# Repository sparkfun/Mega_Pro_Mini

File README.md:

**NOTE:** *This product has been retired from our catalog. If you are looking for more up-to-date info, please check out some of these resources to see how other users are still hacking and improving on this product.*
* *[SparkFun Forum](https://forum.sparkfun.com/)*
* *[Comments Here on GitHub](https://github.com/sparkfun/Mega_Pro_Mini/issues)*
* *[IRC Channel](https://www.sparkfun.com/news/263)*

SparkFun Mega Pro Mini - 3.3V
========================================

[*SparkFun Mega Pro Mini - 3.3V (DEV-10743)*](https://www.sparkfun.com/products/10743)

 This is a 3.3V microcontroller running a version of the stk500v2 bootloader at 8MHz. 
 In order to shrink the Mega Pro down to its minimum footprint, we’ve condensed the board layout, removed the barrel jack footprint and replaced the traditional Arduino-style headers with compact vertical JST connectors.

 Repository Contents
-------------------

* **/Hardware** - Eagle design files (.brd, .sch)
* **/Production** - Production panel files (.brd)

Documentation
--------------
* **[Board Definition Files](https://github.com/sparkfun/Arduino_Boards)** - Board Definition files for Mega Pro Mini. 
* **[SparkFun Fritzing repo](https://github.com/sparkfun/Fritzing_Parts)** - Fritzing diagrams for SparkFun products.
* **[SparkFun 3D Model repo](https://github.com/sparkfun/3D_Models)** - 3D models of SparkFun products. 

License Information
-------------------
This product is _**open source**_! 

The **hardware** is released under [Creative Commons ShareAlike 4.0 International](https://creativecommons.org/licenses/by-sa/4.0/).

Please use, reuse, and modify these files as you see fit. Please maintain attribution to SparkFun Electronics and release anything derivative under the same license.

Distributed as-is; no warranty is given.

- Your friends at SparkFun.

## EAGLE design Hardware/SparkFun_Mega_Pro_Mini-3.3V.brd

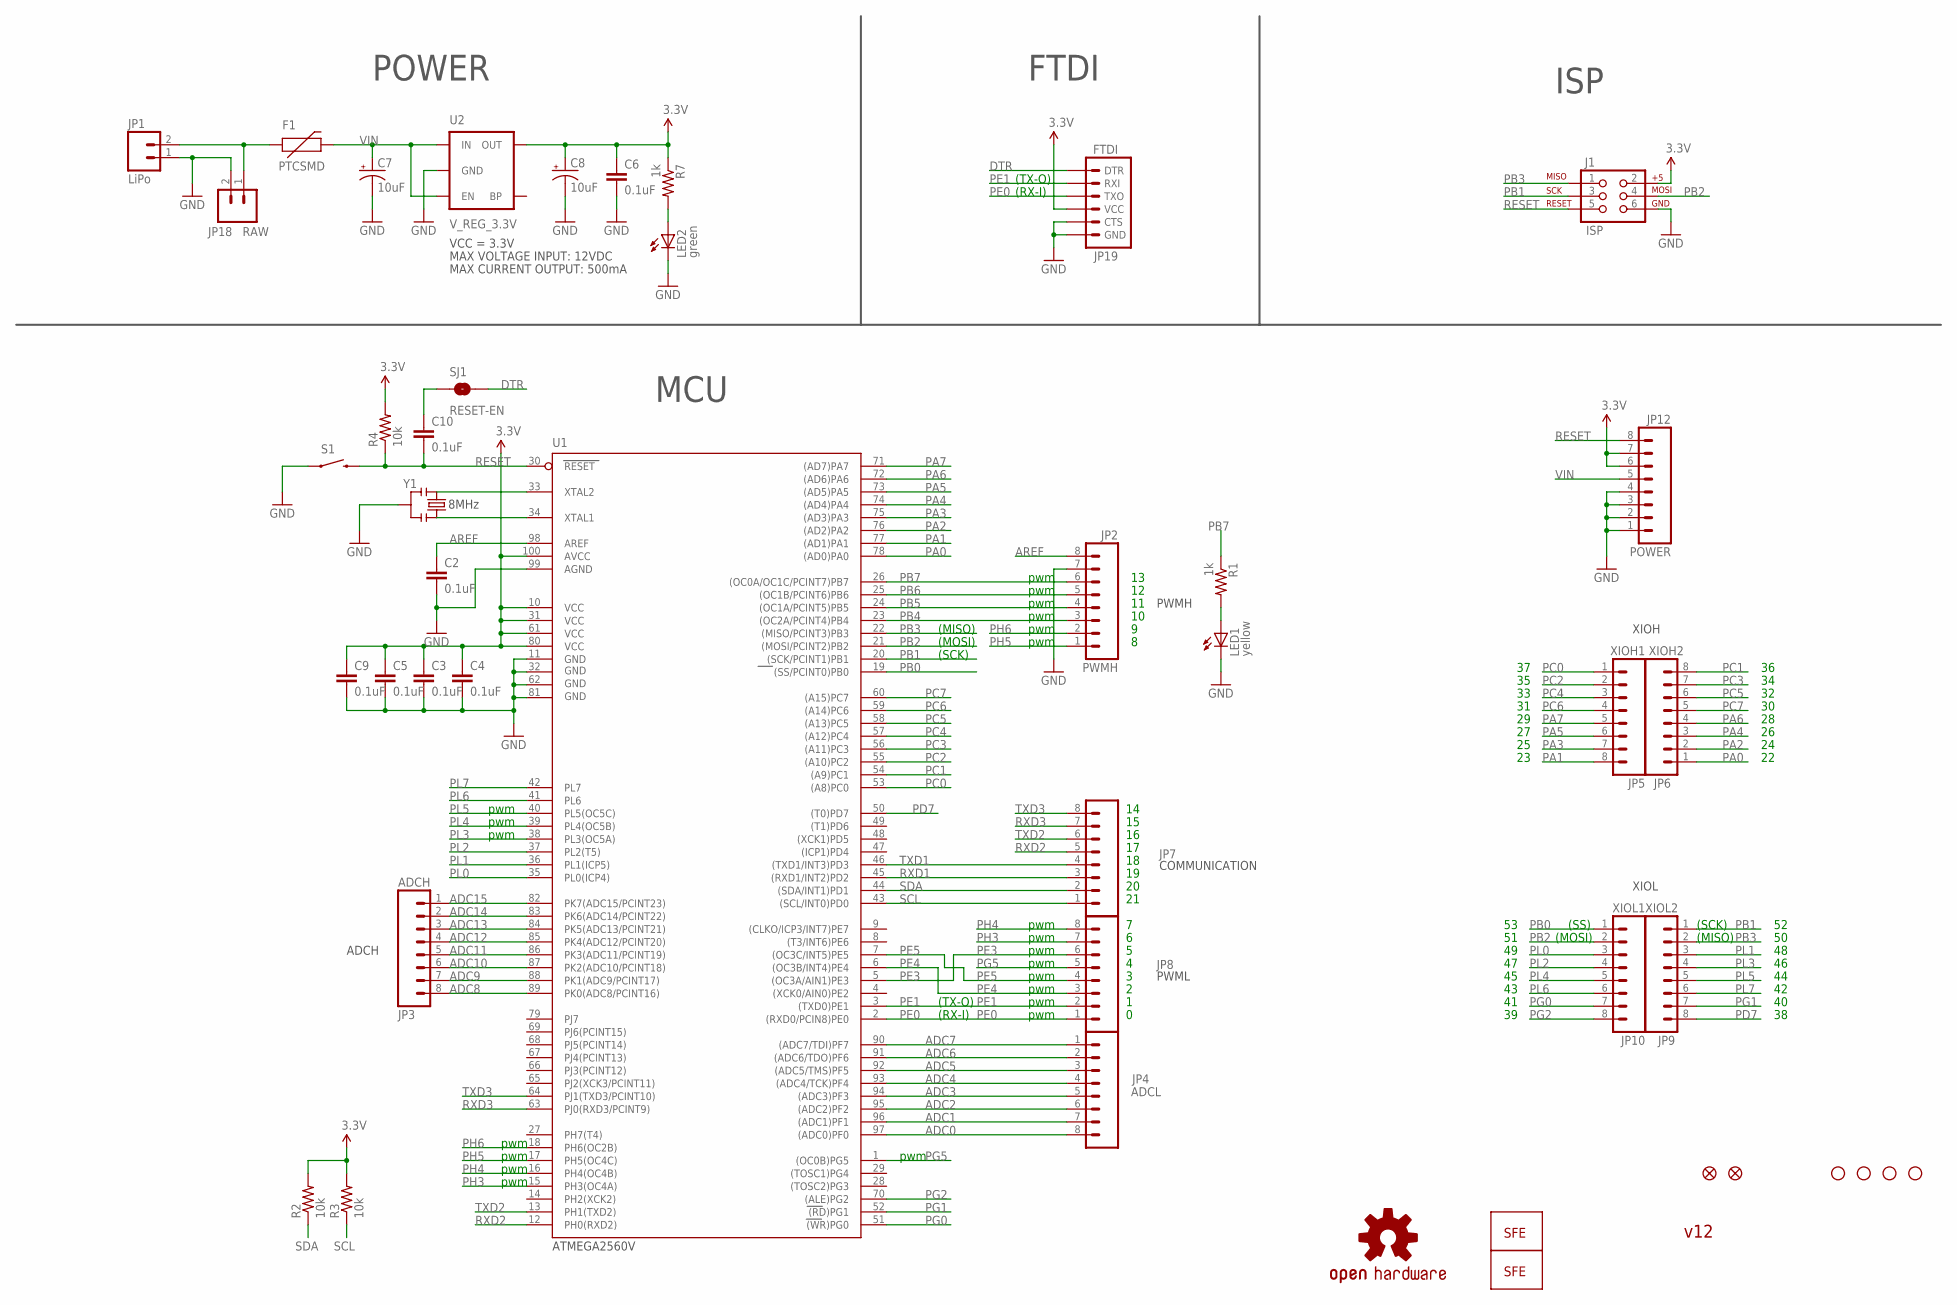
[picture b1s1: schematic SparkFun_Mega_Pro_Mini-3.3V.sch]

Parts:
C2, C3, C4, C5, C6, C9, C10: 0.1uF; 0402-CAP
C7, C8: 10uF; EIA3216
F1: PTCSMD; PTC-1206
J1: ISP; 2X3
JP1: LiPo; JST-2-SMD
JP2: PWMH; BM08B-SRSS-TB
JP3: ADCH; BM08B-SRSS-TB
JP4: ADCL; BM08B-SRSS-TB
JP5: XIOH1; BM08B-SRSS-TB
JP6: XIOH2; BM08B-SRSS-TB
JP7: COMM; BM08B-SRSS-TB
JP8: PWML; BM08B-SRSS-TB
JP9: XIOL2; BM08B-SRSS-TB
JP10: XIOL1; BM08B-SRSS-TB
JP11, JP13, JP14, JP15: STAND-OFF
JP12: POWER; BM08B-SRSS-TB
JP16: LOGO-SFENEW; SFE-NEW-WEBLOGO
JP17: LOGO-SFESK; SFE-LOGO-FLAME
JP18: RAW; 1X02
JP19: FTDI; 1X06-SMD
JP20, JP21: FIDUCIAL1X2.5; FIDUCIAL-1X2.5
LED1: yellow; LED-0603
LED2: green; LED-0603
R1, R7: 1k; 0402-RES
R2, R3, R4: 10k; 0402-RES
S1: SWITCH-MOMENTARY-2SMD; TACTILE_SWITCH_SMD
SJ1: RESET-EN; SJ_2S
U1: ATMEGA2560AU; TQFP100
U2: V_REG_3.3V; SOT23-5
U$9: OSHW-LOGOL; OSHW-LOGO-L
Y1: RESONATORSMD; RESONATOR-SMD

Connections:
3.3V: C3.1, C4.1, C5.1, C6.1, C8.A (+), C9.1, J1.2, JP12.6, JP12.7, JP19.4 (VCC), R2.2, R3.2, R4.2, R7.1, U1.10 (VCC), U1.31 (VCC1), U1.61 (VCC2), U1.80 (VCC3), U1.100 (AVCC), U2.5 (OUT)
ADC0: JP4.8, U1.97 ((ADC0)PF0)
ADC1: JP4.7, U1.96 ((ADC1)PF1)
ADC2: JP4.6, U1.95 ((ADC2)PF2)
ADC3: JP4.5, U1.94 ((ADC3)PF3)
ADC4: JP4.4, U1.93 ((ADC4/TCK)PF4)
ADC5: JP4.3, U1.92 ((ADC5/TMS)PF5)
ADC6: JP4.2, U1.91 ((ADC6/TDO)PF6)
ADC7: JP4.1, U1.90 ((ADC7/TDI)PF7)
ADC8: JP3.8, U1.89 (PK0(ADC8/PCINT16))
ADC9: JP3.7, U1.88 (PK1(ADC9/PCINT17))
ADC10: JP3.6, U1.87 (PK2(ADC10/PCINT18))
ADC11: JP3.5, U1.86 (PK3(ADC11/PCINT19))
ADC12: JP3.4, U1.85 (PK4(ADC12/PCINT20))
ADC13: JP3.3, U1.84 (PK5(ADC13/PCINT21))
ADC14: JP3.2, U1.83 (PK6(ADC14/PCINT22))
ADC15: JP3.1, U1.82 (PK7(ADC15/PCINT23))
AREF: C2.1, JP2.8, U1.98 (AREF)
DTR: JP19.1 (DTR), SJ1.2
GND: C2.2, C3.2, C4.2, C5.2, C6.2, C7.C (-), C8.C (-), C9.2, J1.6, JP1.1, JP2.7, JP12.1, JP12.2, JP12.3, JP12.4, JP18.2, JP19.5 (CTS), JP19.6 (GND), LED1.C, LED2.C, S1.1, U1.11 (GND), U1.32 (GND1), U1.62 (GND2), U1.81 (GND3), U1.99 (AGND), U2.2 (GND), Y1.2
unnamed: F1.1, JP1.2, JP18.1
unnamed: LED1.A, R1.2
unnamed: LED2.A, R7.2
unnamed: U1.34 (XTAL1), Y1.3
unnamed: U1.33 (XTAL2), Y1.1
unnamed: C10.1, SJ1.1
PA0: JP6.1, U1.78 ((AD0)PA0)
PA1: JP5.8, U1.77 ((AD1)PA1)
PA2: JP6.2, U1.76 ((AD2)PA2)
PA3: JP5.7, U1.75 ((AD3)PA3)
PA4: JP6.3, U1.74 ((AD4)PA4)
PA5: JP5.6, U1.73 ((AD5)PA5)
PA6: JP6.4, U1.72 ((AD6)PA6)
PA7: JP5.5, U1.71 ((AD7)PA7)
PB0: JP10.1, U1.19 ((SS/PCINT0)PB0)
PB1: J1.3, JP9.1, U1.20 ((SCK/PCINT1)PB1)
PB2: J1.4, JP10.2, U1.21 ((MOSI/PCINT2)PB2)
PB3: J1.1, JP9.2, U1.22 ((MISO/PCINT3)PB3)
PB4: JP2.3, U1.23 ((OC2A/PCINT4)PB4)
PB5: JP2.4, U1.24 ((OC1A/PCINT5)PB5)
PB6: JP2.5, U1.25 ((OC1B/PCINT6)PB6)
PB7: JP2.6, R1.1, U1.26 ((OC0A/OC1C/PCINT7)PB7)
PC0: JP5.1, U1.53 ((A8)PC0)
PC1: JP6.8, U1.54 ((A9)PC1)
PC2: JP5.2, U1.55 ((A10)PC2)
PC3: JP6.7, U1.56 ((A11)PC3)
PC4: JP5.3, U1.57 ((A12)PC4)
PC5: JP6.6, U1.58 ((A13)PC5)
PC6: JP5.4, U1.59 ((A14)PC6)
PC7: JP6.5, U1.60 ((A15)PC7)
PD7: JP9.8, U1.50 ((T0)PD7)
PE0: JP8.1, JP19.3 (TXO), U1.2 ((RXD0/PCIN8)PE0)
PE1: JP8.2, JP19.2 (RXI), U1.3 ((TXD0)PE1)
PE3: JP8.6, U1.5 ((OC3A/AIN1)PE3)
PE4: JP8.3, U1.6 ((OC3B/INT4)PE4)
PE5: JP8.4, U1.7 ((OC3C/INT5)PE5)
PG0: JP10.7, U1.51 ((WR)PG0)
PG1: JP9.7, U1.52 ((RD)PG1)
PG2: JP10.8, U1.70 ((ALE)PG2)
PG5: JP8.5, U1.1 ((OC0B)PG5)
PH3: JP8.7, U1.15 (PH3(OC4A))
PH4: JP8.8, U1.16 (PH4(OC4B))
PH5: JP2.1, U1.17 (PH5(OC4C))
PH6: JP2.2, U1.18 (PH6(OC2B))
PL0: JP10.3, U1.35 (PL0(ICP4))
PL1: JP9.3, U1.36 (PL1(ICP5))
PL2: JP10.4, U1.37 (PL2(T5))
PL3: JP9.4, U1.38 (PL3(OC5A))
PL4: JP10.5, U1.39 (PL4(OC5B))
PL5: JP9.5, U1.40 (PL5(OC5C))
PL6: JP10.6, U1.41 (PL6)
PL7: JP9.6, U1.42 (PL7)
RESET: C10.2, J1.5, JP12.8, R4.1, S1.3 (2), U1.30 (RESET)
RXD1: JP7.3, U1.45 ((RXD1/INT2)PD2)
RXD2: JP7.5, U1.12 (PH0(RXD2))
RXD3: JP7.7, U1.63 (PJ0(RXD3/PCINT9))
SCL: JP7.1, R3.1, U1.43 ((SCL/INT0)PD0)
SDA: JP7.2, R2.1, U1.44 ((SDA/INT1)PD1)
TXD1: JP7.4, U1.46 ((TXD1/INT3)PD3)
TXD2: JP7.6, U1.13 (PH1(TXD2))
TXD3: JP7.8, U1.64 (PJ1(TXD3/PCINT10))
VIN: C7.A (+), F1.2, JP12.5, U2.1 (IN), U2.3 (EN)

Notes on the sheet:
(SCK)
(MOSI)
(MISO)
(TX-O)
(RX-I)
pwm
(SS)
8MHz
COMMUNICATION
ADCH
PWML
PWMH
XIOH
XIOL
MCU
POWER
FTDI
ATMEGA2560V
ISP
VCC = 3.3V
MAX VOLTAGE INPUT: 12VDC
MAX CURRENT OUTPUT: 500mA
v12

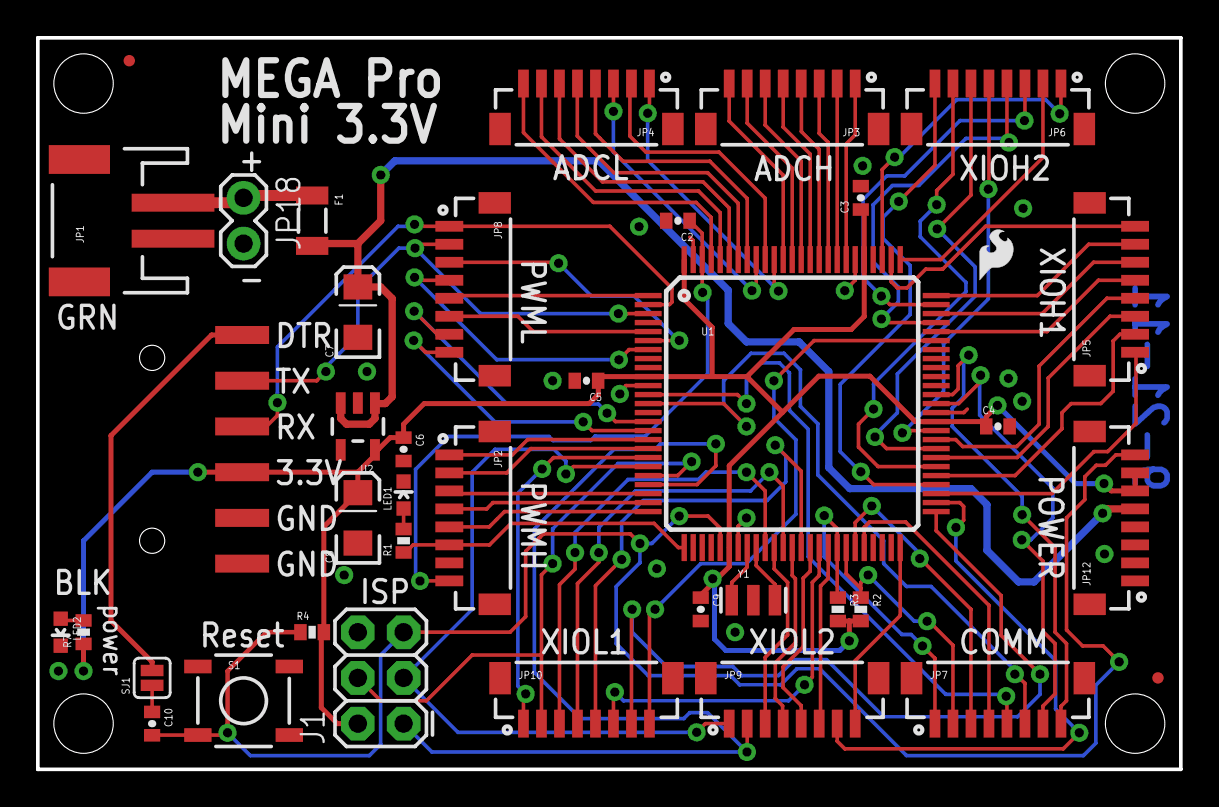
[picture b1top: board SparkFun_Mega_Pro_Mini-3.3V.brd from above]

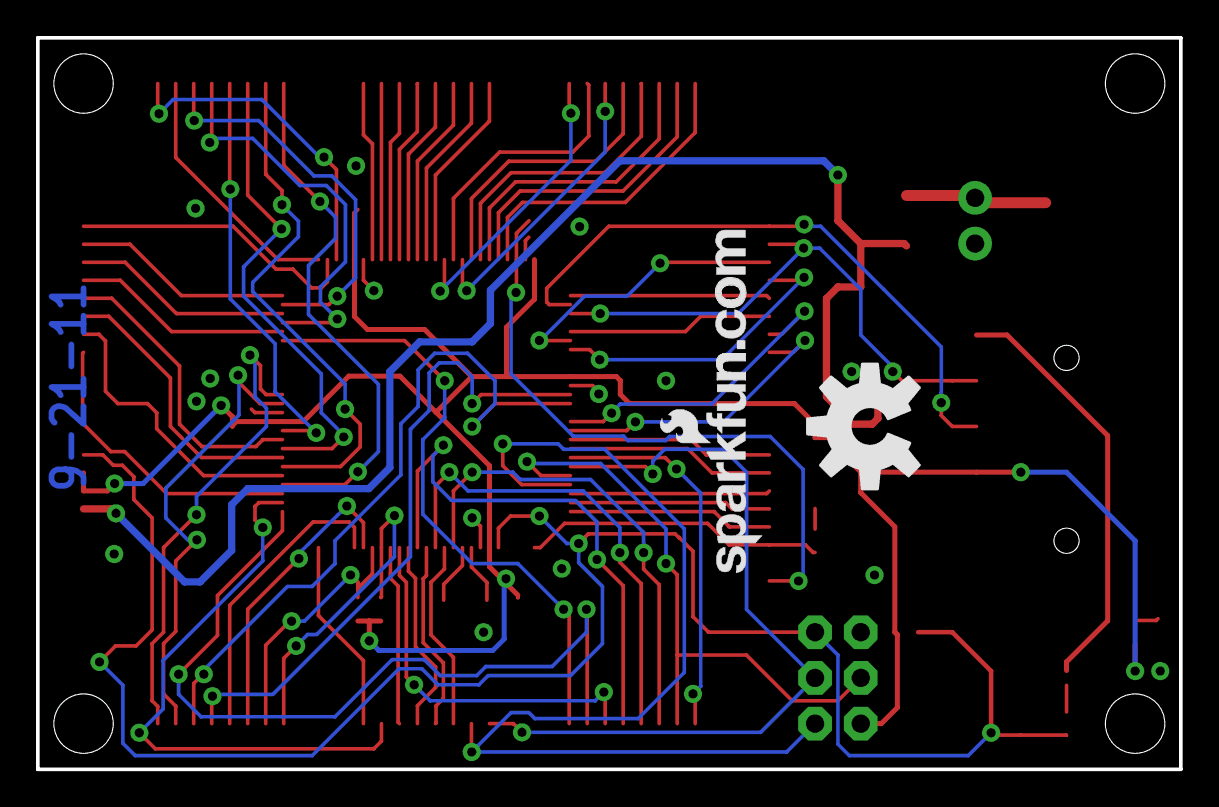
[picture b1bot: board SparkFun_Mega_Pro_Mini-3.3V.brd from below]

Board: 2 copper layers, 63.5 x 40.6 mm, 45 parts (2 on the bottom side), 82 nets.

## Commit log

2015-05-11 Adding hardware files
